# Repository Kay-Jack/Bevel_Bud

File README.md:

# Bezel_Bud
Take a webcam -> remove the camera -> improve the microphone.

- **Status:** Prototype Dev Board
- **Author:** Jack Kay

## Features

- **Feature 1:** 48KHz Dual Microphone - TI PCM1861
- **Feature 2:** Low noise components
- **Feature 3:** Power filtering
- **Feature 4:** 24.576MHz Crystal
- **Feature 5:** Mute switch and Visual LED
- **Feature 6:** Configurable jumpers for ADC
- **Feature 7:** USB-C for connectivity
- **Feature 8:** STM32G431CBT6

## Photos

### Assembly PCB

### Layout

### Schematic

## Firmware / Electronics

[WIP]

## CAD / Mechanical

[WIP]

## Build Instructions

[WIP]

## Usage

[WIP]

## License

This project is licensed under the terms in the `LICENSE` file.

## Contact

Maintainer: Jack Kay — jack.wil.kay@gmail.com

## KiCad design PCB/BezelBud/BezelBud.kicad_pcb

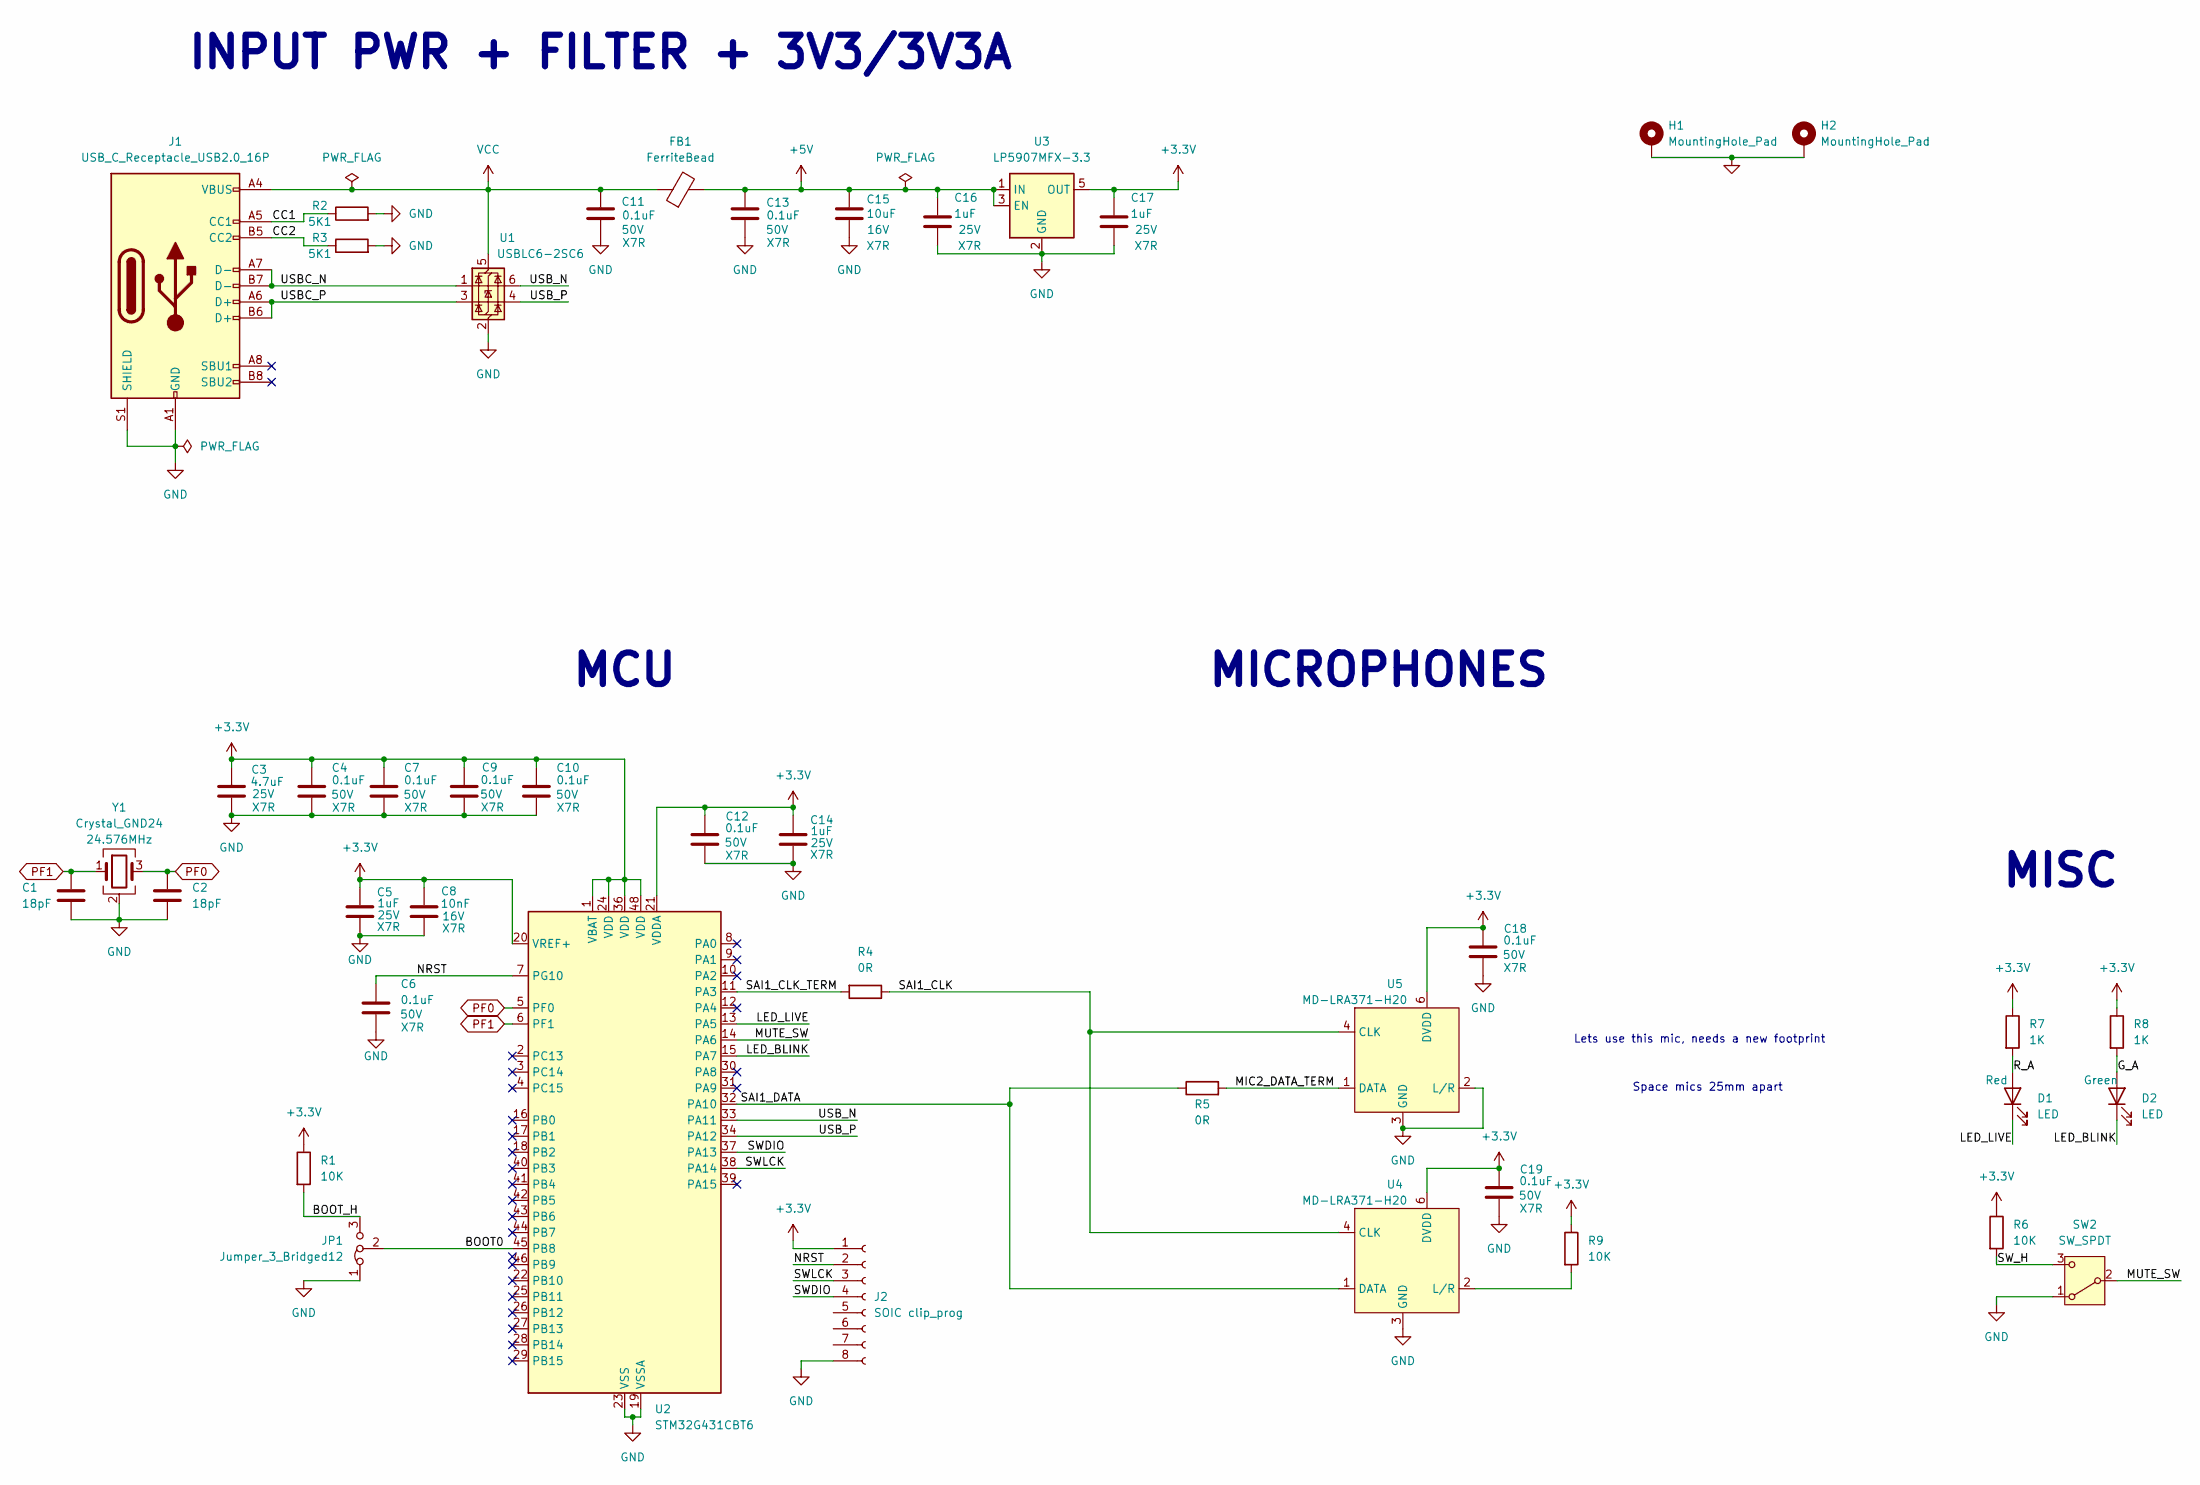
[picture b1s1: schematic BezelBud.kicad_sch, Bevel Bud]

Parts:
C1, C2: 18pF; C_0603_1608Metric
C3: 4.7uF; C_0805_2012Metric; Voltage 25V; Rating X7R
C4, C6, C7, C9, C10, C11, C12, C13, C18, C19: 0.1uF; C_0603_1608Metric; Voltage 50V; Rating X7R
C5, C14, C16, C17: 1uF; C_0805_2012Metric; Voltage 25V; Rating X7R
C8: 10nF; C_0603_1608Metric; Rating X7R; Voltage 16V
C15: 10uF; C_0805_2012Metric; Voltage 16V; Rating X7R
D1, D2: LED; LED_0603_1608Metric
FB1: FerriteBead; L_0805_2012Metric
H1, H2: MountingHole_Pad; MountingHole_3.2mm_M3_Pad_Via
J1: USB_C_Receptacle_USB2.0_16P; USB_C_Receptacle_G-Switch_GT-USB-7010ASV
J2: SOIC clip_prog; SOIC_clipProgSmall
JP1: Jumper_3_Bridged12
R1, R6, R9: 10K; R_0603_1608Metric
R2, R3: 5K1; R_0603_1608Metric
R4, R5: 0R; R_0603_1608Metric
R7, R8: 1K; R_0603_1608Metric
SW2: SW_SPDT; SW_SPDT_Shouhan_MSK12C02
U1: USBLC6-2SC6; SOT-23-6
U2: STM32G431CBT6; LQFP-48_7x7mm_P0.5mm
U3: LP5907MFX-3.3; SOT-23-5
U4, U5: MD-LRA371-H20
Y1: Crystal_GND24; Crystal_SMD_3225-4Pin_3.2x2.5mm

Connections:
+3.3V: C3.1, C4.1, C5.1, C7.1, C8.1, C9.1, C10.1, C12.1, C14.1, C17.1, C18.1, C19.1, J2.1, R1.1, R6.1, R7.1, R8.1, R9.1, U2.1 (VBAT), U2.20 (VREF+), U2.21 (VDDA), U2.24 (VDD), U2.36 (VDD), U2.48 (VDD), U3.5 (OUT), U4.5 (AVDD), U4.6 (DVDD), U5.5 (AVDD), U5.6 (DVDD)
+5V: C13.1, C15.1, C16.1, FB1.2, U3.1 (IN), U3.3 (EN)
/BOOT0: JP1.2 (C), U2.45 (PB8)
/BOOT_H: JP1.3 (B), R1.2
/CC1: J1.A5 (CC1), R2.1
/CC2: J1.B5 (CC2), R3.1
/G_A: D2.2 (A), R8.2
/LED_BLINK: D2.1 (K), U2.15 (PA7)
/LED_LIVE: D1.1 (K), U2.13 (PA5)
/MIC2_DATA_TERM: R5.2, U5.1 (DATA)
/MUTE_SW: SW2.2 (B), U2.14 (PA6)
/NRST: C6.1, J2.2, U2.7 (PG10)
/R_A: D1.2 (A), R7.2
/SAI1_CLK: R4.1, U4.4 (CLK), U5.4 (CLK)
/SAI1_CLK_TERM: R4.2, U2.11 (PA3)
/SAI1_DATA: R5.1, U2.32 (PA10), U4.1 (DATA)
/SWDIO: J2.4, U2.37 (PA13)
/SWLCK: J2.3, U2.38 (PA14)
/SW_H: R6.2, SW2.3 (C)
/USBC_N: J1.A7 (D-), J1.B7 (D-), U1.1 (I/O1)
/USBC_P: J1.A6 (D+), J1.B6 (D+), U1.3 (I/O2)
/USB_N: U1.6 (I/O1), U2.33 (PA11)
/USB_P: U1.4 (I/O2), U2.34 (PA12)
GND: C1.2, C2.2, C3.2, C4.2, C5.2, C6.2, C7.2, C8.2, C9.2, C10.2, C11.2, C12.2, C13.2, C14.2, C15.2, C16.2, C17.2, C18.2, C19.2, H1.1, H2.1, J1.A1 (GND), J1.A12 (GND), J1.B1 (GND), J1.B12 (GND), J1.S1 (SHIELD), J2.8, JP1.1 (A), R2.2, R3.2, SW2.1 (A), U1.2 (GND), U2.19 (VSSA), U2.23 (VSS), U2.35 (VSS), U2.47 (VSS), U3.2 (GND), U4.3 (GND), U5.2 (L/R), U5.3 (GND), Y1.2 (G), Y1.4 (G)
unnamed: R9.2, U4.2 (L/R)
PF0: C2.1, U2.5 (PF0), Y1.3
PF1: C1.1, U2.6 (PF1), Y1.1
VCC: C11.1, FB1.1, J1.A4 (VBUS), J1.A9 (VBUS), J1.B4 (VBUS), J1.B9 (VBUS), U1.5 (VBUS)

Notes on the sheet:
MCU
MICROPHONES
Lets use this mic, needs a new footprint
MISC
INPUT PWR + FILTER + 3V3/3V3A
Space mics 25mm apart

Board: 2 copper layers, 41 parts (0 on the bottom side), 28 nets, no tracks yet.

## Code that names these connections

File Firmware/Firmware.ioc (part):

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Mcu.Name=STM32G431C(6-8-B)Tx
Mcu.Package=LQFP48
Mcu.UserName=STM32G431CBTx
PA11.Mode=Device
PA11.Signal=USB_DM
PA12.Mode=Device
PA12.Signal=USB_DP
PA13.Mode=Serial_Wire
PA13.Signal=SYS_JTMS-SWDIO
PA14.Mode=Serial_Wire
PA14.Signal=SYS_JTCK-SWCLK
PA15.GPIOParameters=GPIO_Label
PA15.GPIO_Label=LED_LIVE
PA15.Signal=GPIO_Output
PA8.Mode=Master_Clock_Activated
PA8.Signal=I2S2_MCK
PB11.GPIOParameters=GPIO_Label
PB11.GPIO_Label=INTRPT
PB11.Signal=GPIO_Input
PB12.Mode=Half_Duplex_Master
PB12.Signal=I2S2_WS
PB13.Mode=Half_Duplex_Master
PB13.Signal=I2S2_CK
PB15.Mode=Half_Duplex_Master
PB15.Signal=I2S2_SD
PB3.GPIOParameters=GPIO_Label
PB3.GPIO_Label=MUTE_SW
PB3.Signal=GPIO_Input
PB4.GPIOParameters=GPIO_Label
PB4.GPIO_Label=LED_BLINK
PB4.Signal=GPIO_Output
PB8-BOOT0.GPIOParameters=GPIO_Label
PB8-BOOT0.GPIO_Label=Boot0
PB8-BOOT0.Signal=GPIO_Output
PF0-OSC_IN.Mode=HSE-External-Oscillator
PF0-OSC_IN.Signal=RCC_OSC_IN
PF1-OSC_OUT.Mode=HSE-External-Oscillator
PF1-OSC_OUT.Signal=RCC_OSC_OUT
RCC.HSE_VALUE=24576000
RCC.SYSCLKFreq_VALUE=49152000
RCC.SYSCLKSource=RCC_SYSCLKSOURCE_PLLCLK
board=custom

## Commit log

2026-01-30 Initialized PCB and STM32Cube
2026-02-02 Added parts to schematic
2026-02-05 updated firmware and schematic
2026-02-10 Finalized component selection
    Selected caps, ratings and footprints. Added crystal to codec
    Added Interrupt
    Wired master clk as backup
    updated cubeMX to match
2026-02-10 Added Footprint for Crystal and Microphone
2026-02-12 Numerous quality of life changes and started PCB Design
    - Configuration pins
    - 16P USBC
    - Removed Microphone pads, will be using a small 2 pin pad for now
    - reduced part count if possible
2026-02-12 Swapped MCU to M4 need to update schematic
2026-02-13 small updates to schematic and layout for new stm32
2026-02-13 updated pcb layout
2026-02-14 Updated PCB
2026-02-14 Added bleed resistor and cap to shield <> GND con
2026-02-15 updated layout picture
2026-02-15 remapped int pin to avoid crossing
2026-02-15 saved schem
2026-02-15 removed usb decoupling and moved blink and led vias
2026-02-15 updated size of pcb to be round numbers
2026-02-16 updated photos
2026-02-19 Updated to different Mic and finished PCB
2026-02-19 updated schem
2026-04-15 deleted gerbers and fixed LED orientation
2026-04-15 Moved Led by switch, moved mute led and mute switch to closer pin
2026-04-15 added suppliers for some parts
2026-04-16 updated footprints for mic and debug
    started pcb layout
2026-04-23 Starting layout for scored and mouse bite PCB
